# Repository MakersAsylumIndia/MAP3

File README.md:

# MAP3

**Maker's Asylum Project #3**

Learn a lot project

***FEATURES***

1. A handy Torch with 4 (or 3) White LED's powered by a 9V battery.
2. Includes one fixed current limiting resistor.
3. Includes a secondary variable trimpot (potentiometer) to allow dimming.

***LEARN***

1. Learn PCB design using KiCad
2. Learn Enclosure design using FreeCAD
3. Learn PCB Production (using Laser Cutter exposing and Ferric Chloride etching) and Manual Drilling
4. Learn to Solder
5. Learn 3D Printing

DISCUSSION FORUM : TBD

Through Hole Version

Inspired by the PT-3000 Personal Torch as shown on Adafruit at
https://learn.adafruit.com/pt3000-personal-torch/

License
-------
[CERN Open Hardware Licence v1.2 ]

[CERN Open Hardware Licence v1.2 ]:http://www.ohwr.org/attachments/2388/cern_ohl_v_1_2.txt

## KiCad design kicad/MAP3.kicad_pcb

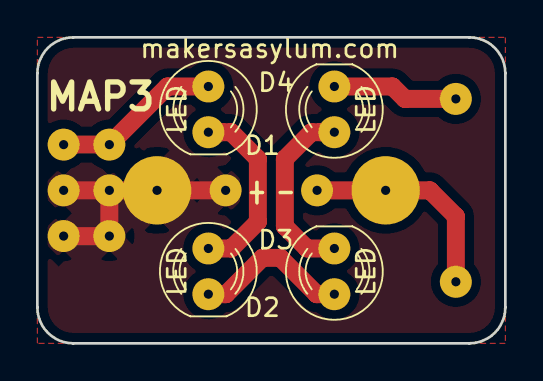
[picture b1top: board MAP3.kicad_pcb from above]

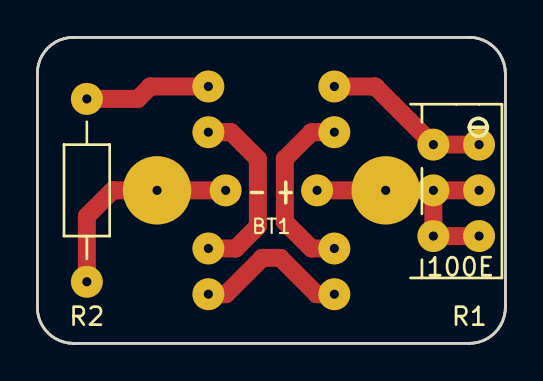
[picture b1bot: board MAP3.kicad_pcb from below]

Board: 2 copper layers, 26.0 x 17.0 mm, 7 parts (3 on the bottom side), 7 nets.

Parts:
BT1: BATT_HOLDER; 9V_clip_968
D1, D2, D3, D4: LED; LED-5MM
R1: 100E; Potentiometer_Bourns_3296Y_3-8Zoll_Angular_ScrewUp
R2: 100E; Resistor_Horizontal_RM10mm

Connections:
/[+]: BT1.1, R1.2, R1.3
/[-]: BT1.2, R2.2
unnamed: D1.1, R1.1
unnamed: D1.2, D2.1
unnamed: D2.2, D3.1
unnamed: D3.2, D4.1
unnamed: D4.2, R2.1

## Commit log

2016-04-18 MAP3 design complete. Versatile Learning Project - see readme for details
2016-04-18 edited README.md
